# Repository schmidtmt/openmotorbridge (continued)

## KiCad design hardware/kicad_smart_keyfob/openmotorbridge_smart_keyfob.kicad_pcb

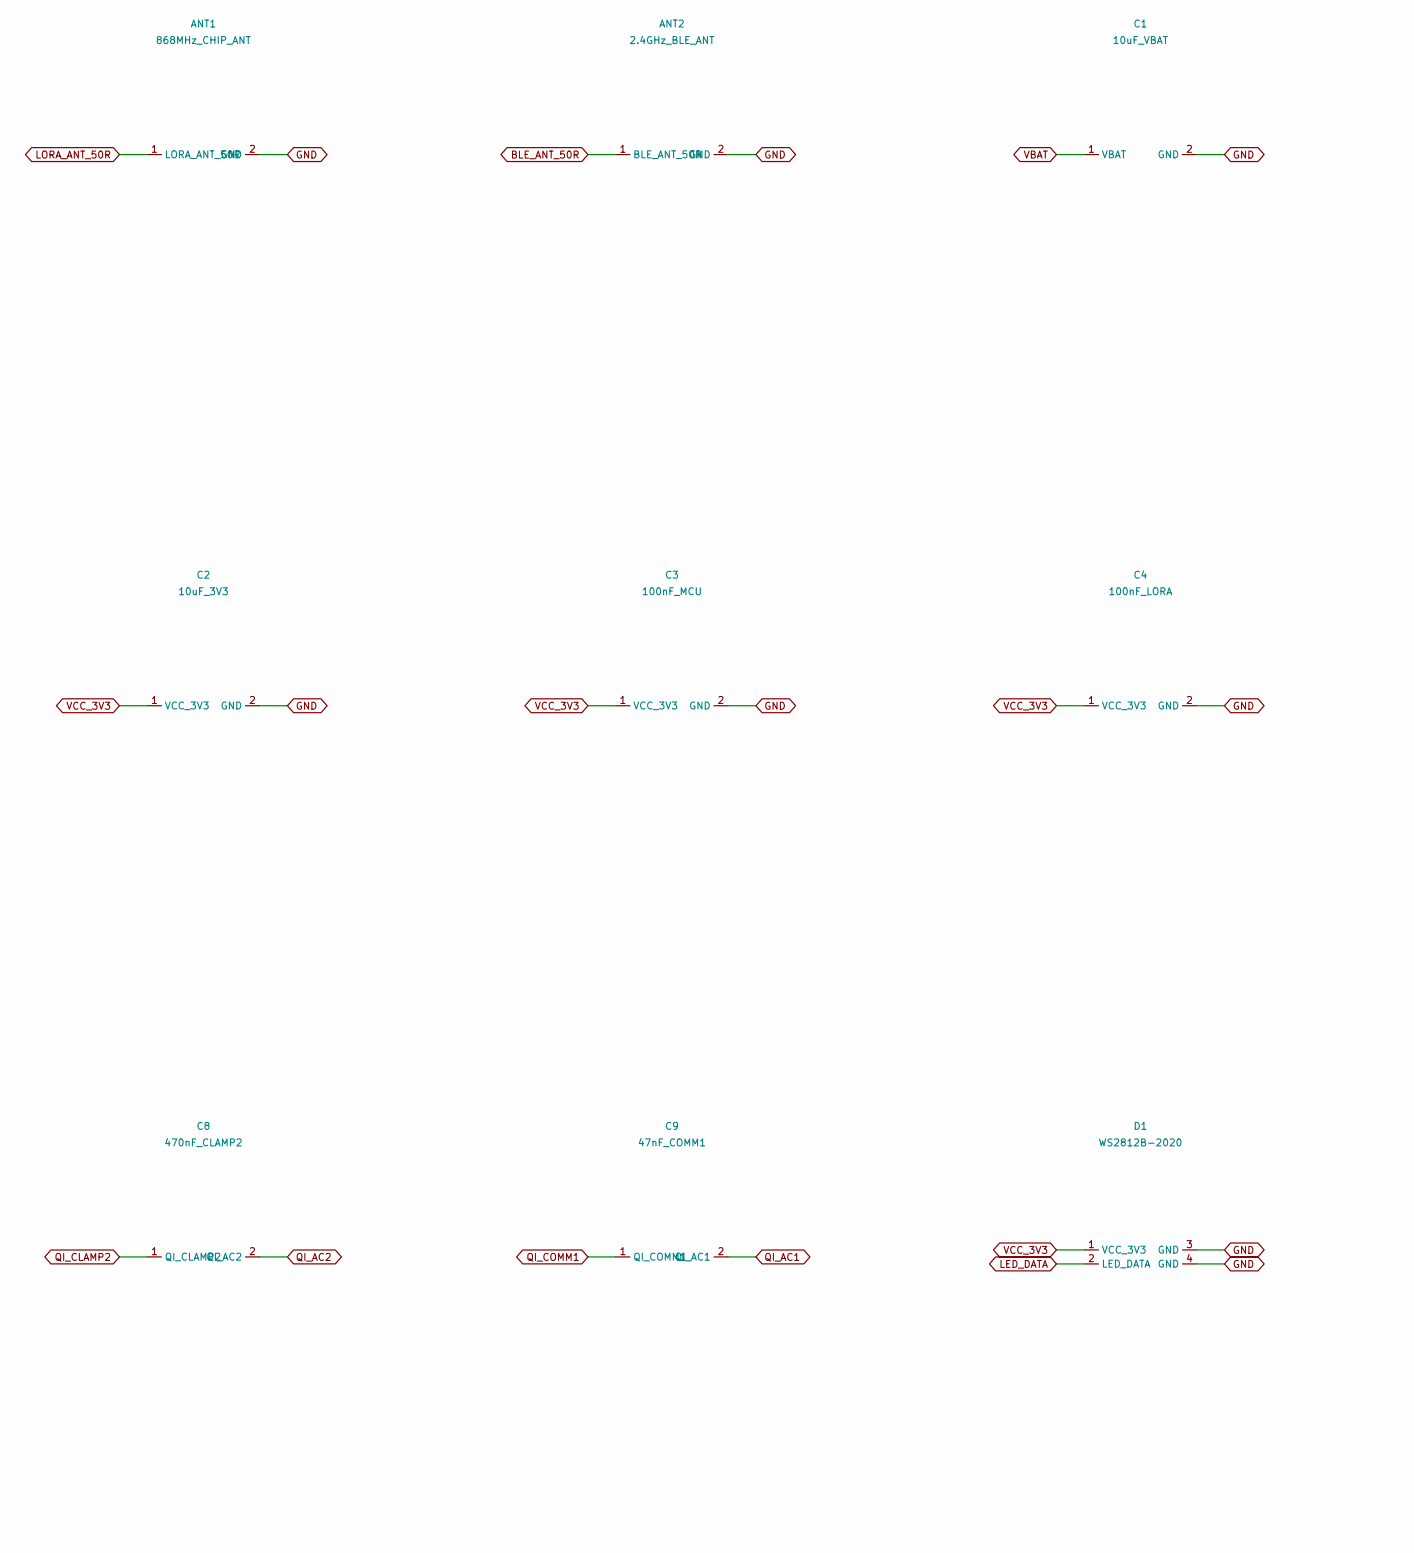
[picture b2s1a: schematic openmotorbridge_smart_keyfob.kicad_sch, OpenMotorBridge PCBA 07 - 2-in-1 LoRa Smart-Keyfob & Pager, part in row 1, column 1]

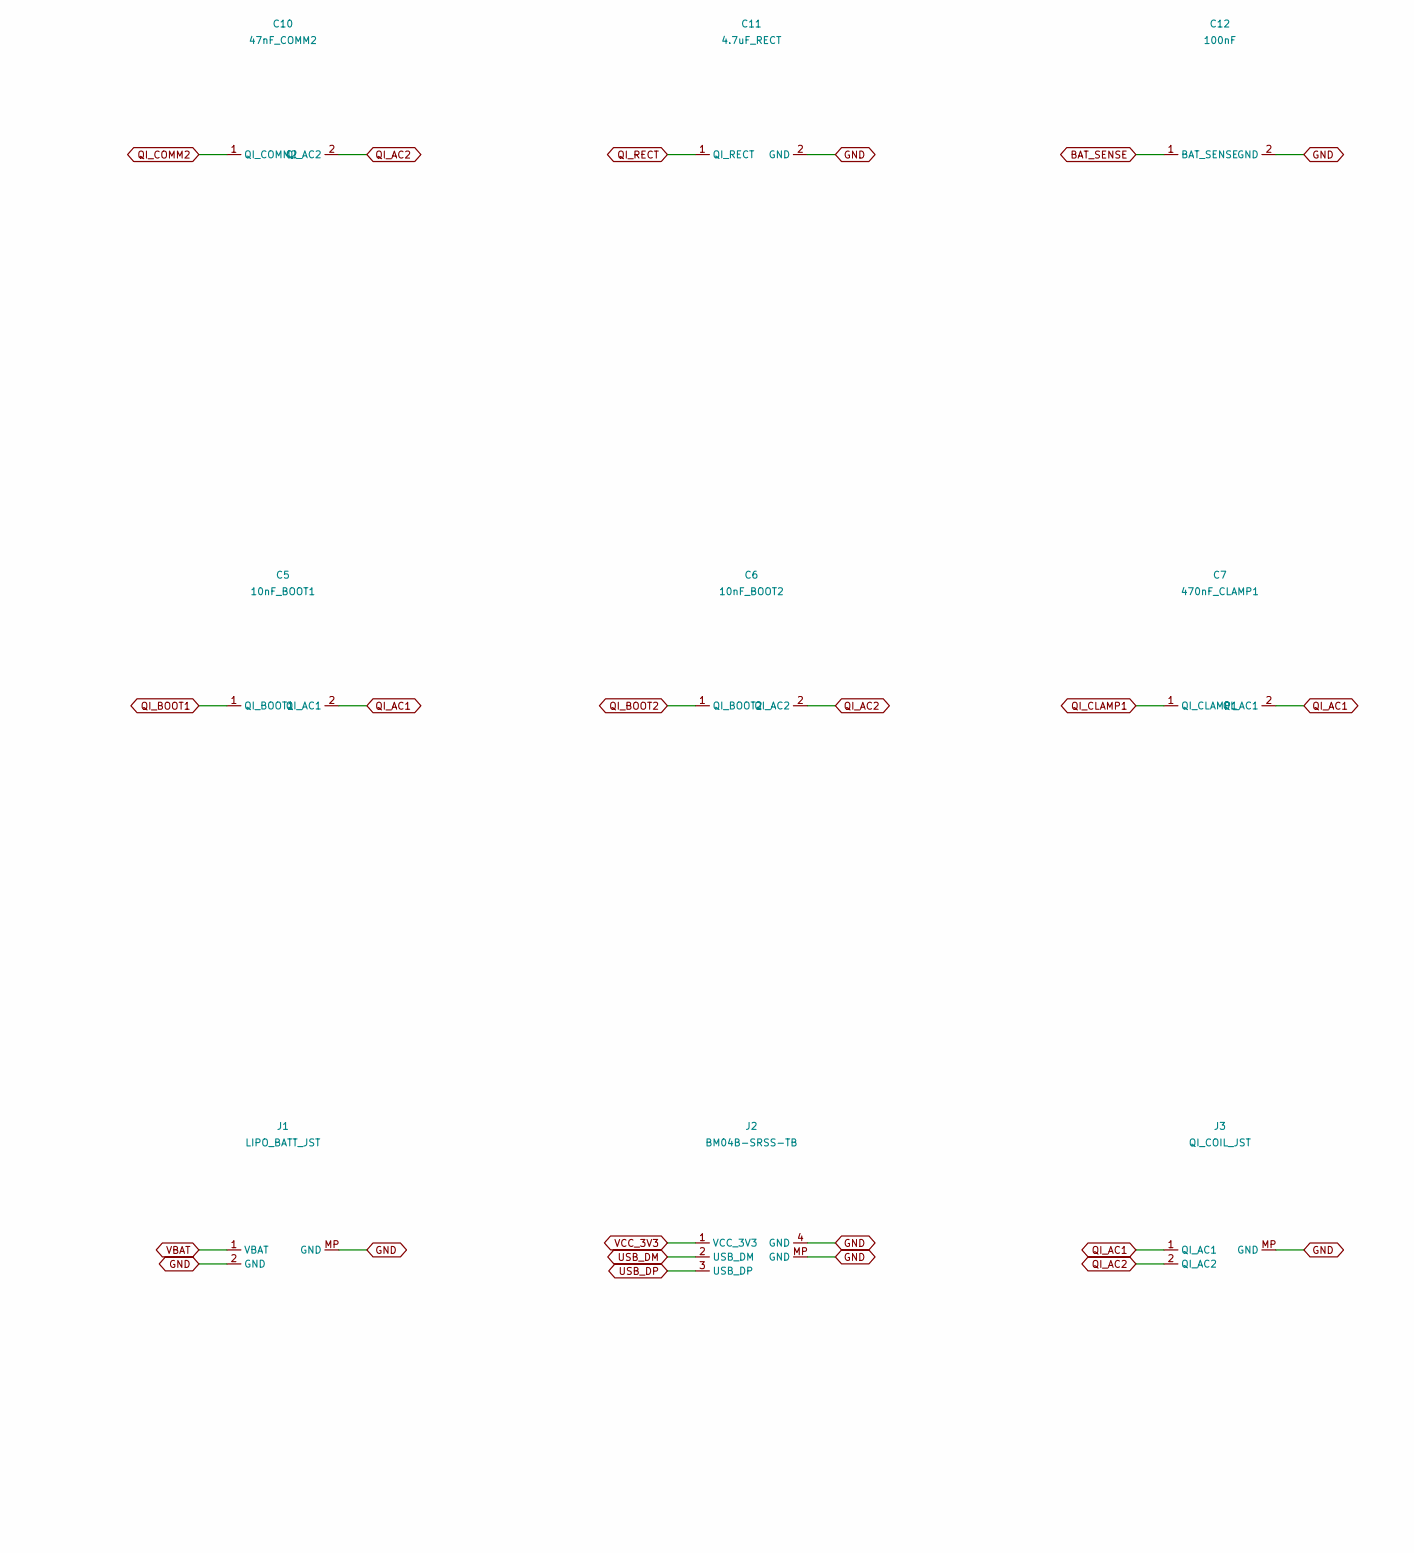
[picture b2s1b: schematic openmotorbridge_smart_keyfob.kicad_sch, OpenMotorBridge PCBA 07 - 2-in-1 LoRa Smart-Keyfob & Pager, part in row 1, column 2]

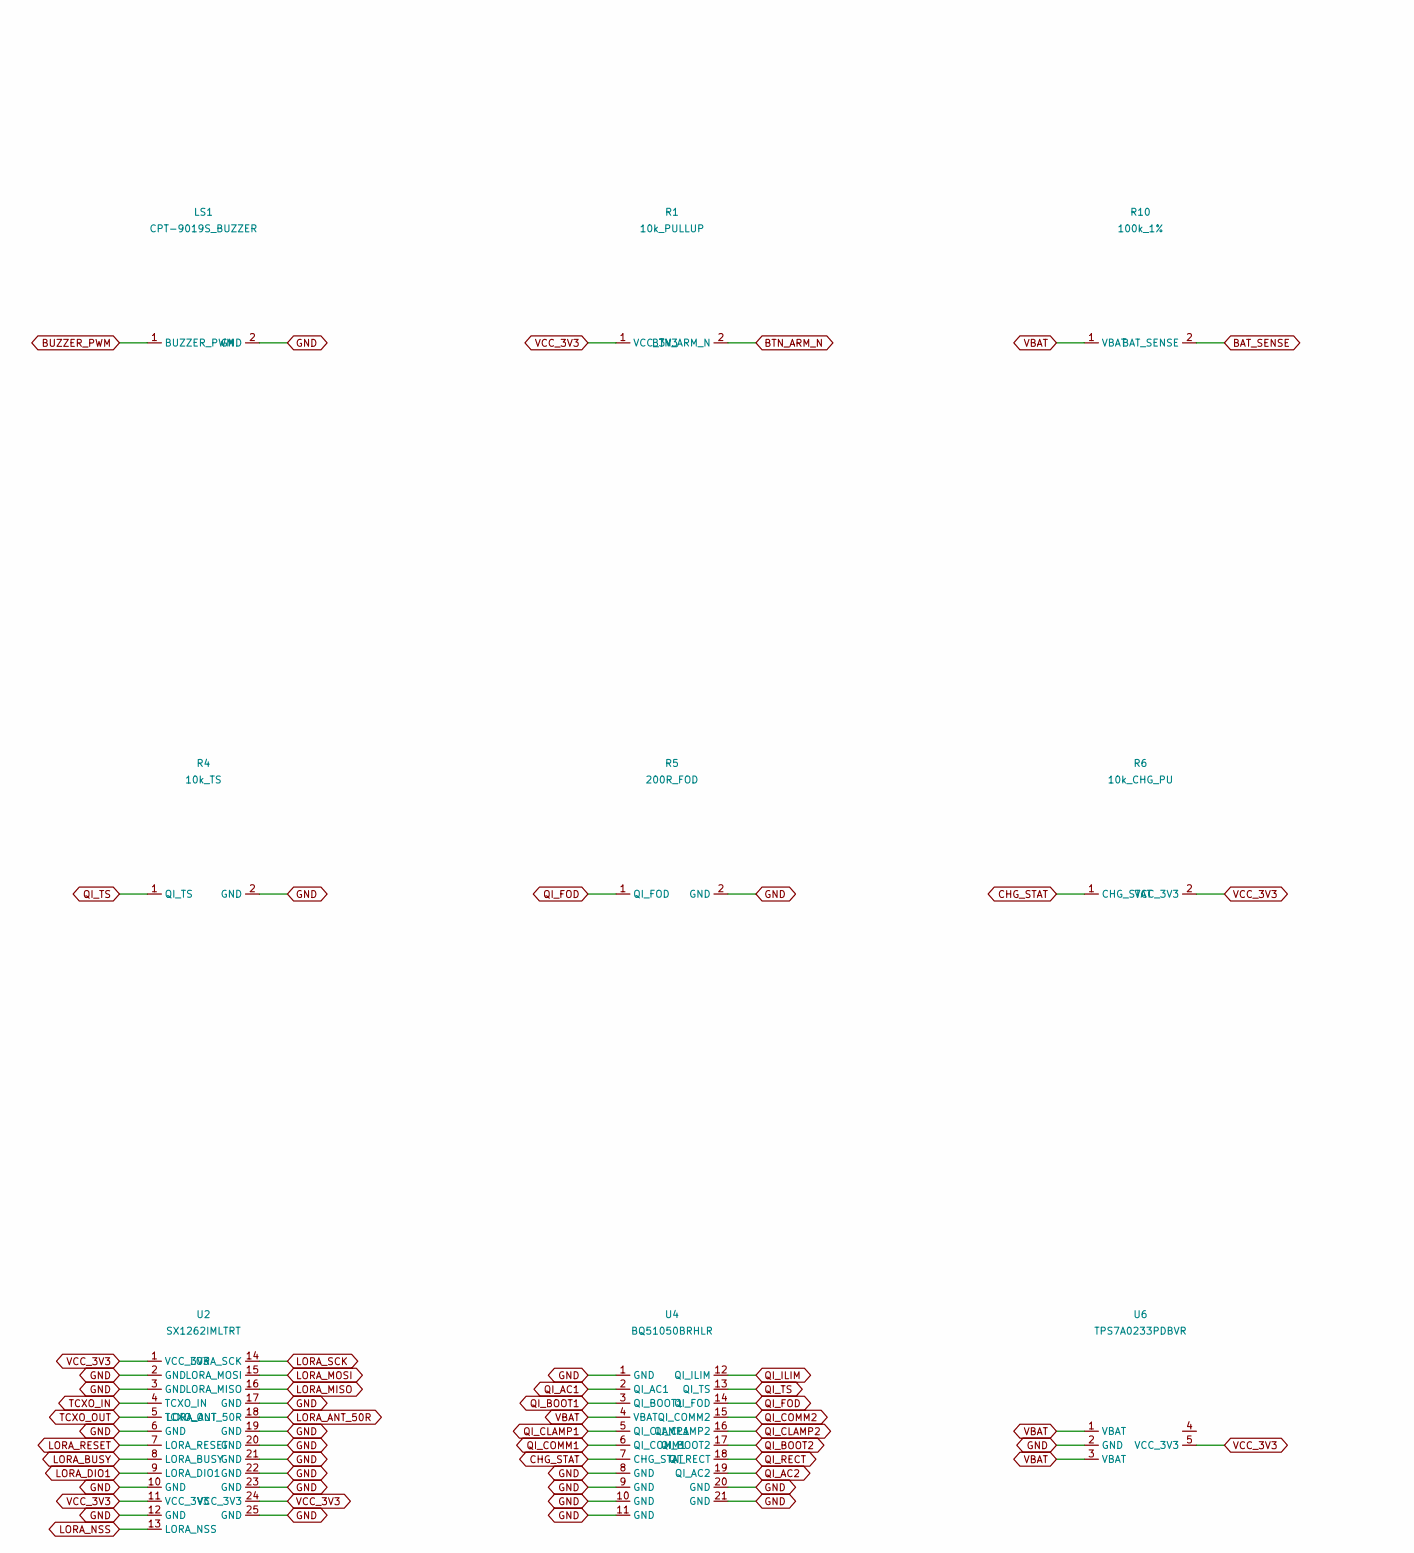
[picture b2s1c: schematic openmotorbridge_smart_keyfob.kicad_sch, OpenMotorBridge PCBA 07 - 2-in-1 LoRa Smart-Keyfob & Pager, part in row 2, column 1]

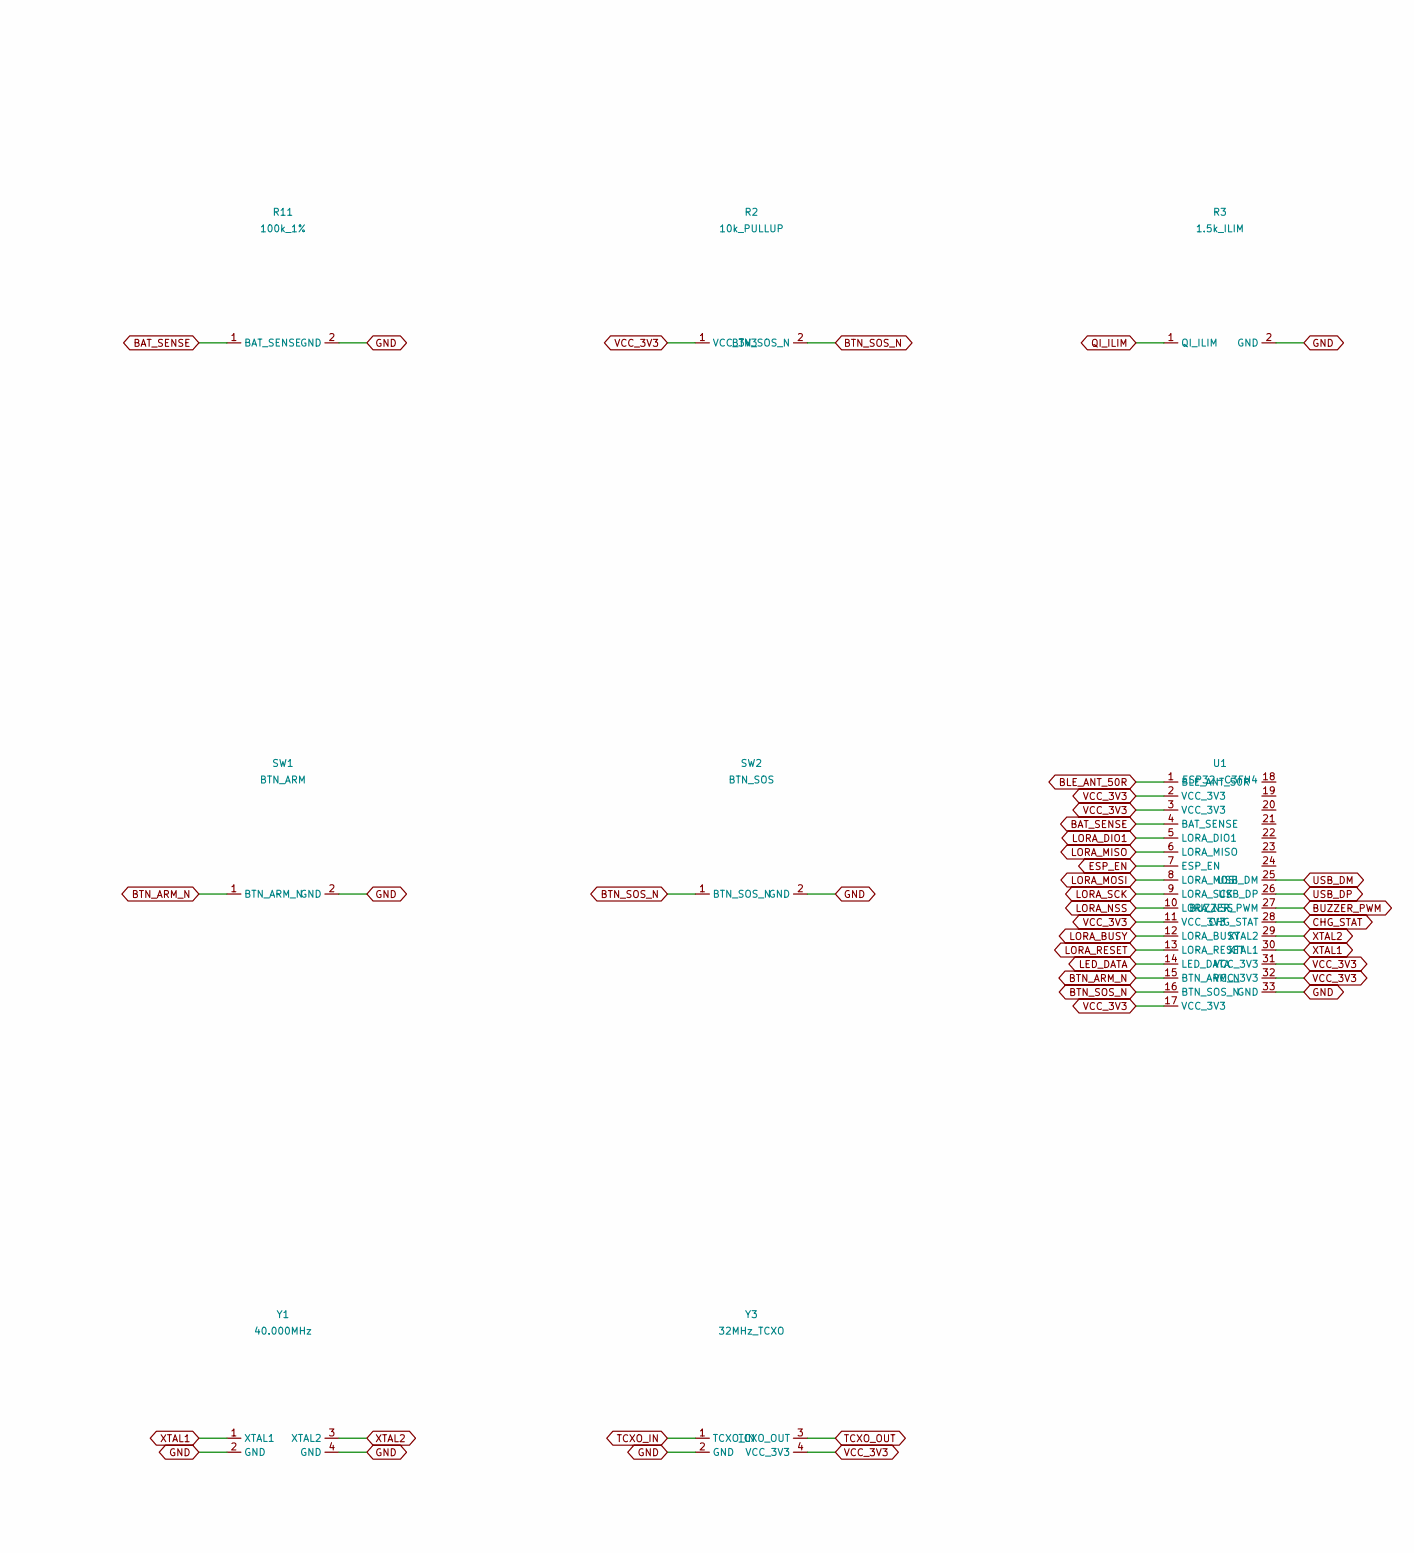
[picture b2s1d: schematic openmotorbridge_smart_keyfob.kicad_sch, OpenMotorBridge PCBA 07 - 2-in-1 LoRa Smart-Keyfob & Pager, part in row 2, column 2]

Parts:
ANT1: 868MHz_CHIP_ANT; R_0805_2012Metric
ANT2: 2.4GHz_BLE_ANT; R_0805_2012Metric
C1: 10uF_VBAT; C_0603_1608Metric
C2: 10uF_3V3; C_0603_1608Metric
C3: 100nF_MCU; C_0402_1005Metric
C4: 100nF_LORA; C_0402_1005Metric
C5: 10nF_BOOT1; C_0402_1005Metric
C6: 10nF_BOOT2; C_0402_1005Metric
C7: 470nF_CLAMP1; C_0402_1005Metric
C8: 470nF_CLAMP2; C_0402_1005Metric
C9: 47nF_COMM1; C_0402_1005Metric
C10: 47nF_COMM2; C_0402_1005Metric
C11: 4.7uF_RECT; C_0402_1005Metric
C12: 100nF; C_0402_1005Metric
D1: WS2812B-2020; LED_WS2812B-2020_PLCC4_2.0x2.0mm
J1: LIPO_BATT_JST; JST_SH_BM02B-SRSS-TB_1x02-1MP_P1.00mm_Vertical
J2: BM04B-SRSS-TB; JST_SH_BM04B-SRSS-TB_1x04-1MP_P1.00mm_Vertical
J3: QI_COIL_JST; JST_SH_BM02B-SRSS-TB_1x02-1MP_P1.00mm_Vertical
LS1: CPT-9019S_BUZZER; Buzzer_CUI_CPT-9019S-SMT
R1, R2: 10k_PULLUP; R_0402_1005Metric
R3: 1.5k_ILIM; R_0402_1005Metric
R4: 10k_TS; R_0402_1005Metric
R5: 200R_FOD; R_0402_1005Metric
R6: 10k_CHG_PU; R_0402_1005Metric
R10, R11: 100k_1%; R_0402_1005Metric
SW1: BTN_ARM; SW_Push_SPST_NO_Alps_SKRK
SW2: BTN_SOS; SW_Push_SPST_NO_Alps_SKRK
U1: ESP32-C3FH4; QFN-32-1EP_5x5mm_P0.5mm_EP3.7x3.7mm_ThermalVias
U2: SX1262IMLTRT; QFN-24-1EP_4x4mm_P0.5mm_EP2.8x2.8mm
U4: BQ51050BRHLR; Texas_VQFN-RHL-20_ThermalVias
U6: TPS7A0233PDBVR; SOT-23-5
Y1: 40.000MHz; Crystal_SMD_2016-4Pin_2.0x1.6mm
Y3: 32MHz_TCXO; Crystal_SMD_2016-4Pin_2.0x1.6mm

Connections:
BAT_SENSE: C12.1 (BAT_SENSE), R10.2 (BAT_SENSE), R11.1 (BAT_SENSE), U1.4 (BAT_SENSE)
BLE_ANT_50R: ANT2.1 (BLE_ANT_50R), U1.1 (BLE_ANT_50R)
BTN_ARM_N: R1.2 (BTN_ARM_N), SW1.1 (BTN_ARM_N), U1.15 (BTN_ARM_N)
BTN_SOS_N: R2.2 (BTN_SOS_N), SW2.1 (BTN_SOS_N), U1.16 (BTN_SOS_N)
BUZZER_PWM: LS1.1 (BUZZER_PWM), U1.27 (BUZZER_PWM)
CHG_STAT: R6.1 (CHG_STAT), U1.28 (CHG_STAT), U4.7 (CHG_STAT)
ESP_EN: U1.7 (ESP_EN)
GND: ANT1.2 (GND), ANT2.2 (GND), C1.2 (GND), C2.2 (GND), C3.2 (GND), C4.2 (GND), C11.2 (GND), C12.2 (GND), D1.3 (GND), D1.4 (GND), J1.2 (QI_AC2), J1.MP, J2.4 (GND), J2.MP, J3.MP, LS1.2 (GND), R3.2 (GND), R4.2 (GND), R5.2 (GND), R11.2 (GND), SW1.2 (GND), SW2.2 (GND), U1.33 (GND), U2.2 (GND), U2.3 (GND), U2.6 (GND), U2.10 (GND), U2.12 (GND), U2.17 (GND), U2.19 (GND), U2.20 (GND), U2.21 (GND), U2.22 (GND), U2.23 (GND), U2.25 (GND), U4.1 (GND), U4.8 (GND), U4.9 (GND), U4.10 (GND), U4.11 (GND), U4.20 (GND), U4.21 (GND), U6.2 (GND), Y1.2 (GND), Y1.4 (GND), Y3.2 (GND)
LED_DATA: D1.2 (LED_DATA), U1.14 (LED_DATA)
LORA_ANT_50R: ANT1.1 (LORA_ANT_50R), U2.18 (LORA_ANT_50R)
LORA_BUSY: U1.12 (LORA_BUSY), U2.8 (LORA_BUSY)
LORA_DIO1: U1.5 (LORA_DIO1), U2.9 (LORA_DIO1)
LORA_MISO: U1.6 (LORA_MISO), U2.16 (LORA_MISO)
LORA_MOSI: U1.8 (LORA_MOSI), U2.15 (LORA_MOSI)
LORA_NSS: U1.10 (LORA_NSS), U2.13 (LORA_NSS)
LORA_RESET: U1.13 (LORA_RESET), U2.7 (LORA_RESET)
LORA_SCK: U1.9 (LORA_SCK), U2.14 (LORA_SCK)
QI_AC1: C5.2 (QI_AC1), C7.2 (QI_AC1), C9.2 (QI_AC1), J3.1 (VBAT), U4.2 (QI_AC1)
QI_AC2: C6.2 (QI_AC2), C8.2 (QI_AC2), C10.2 (QI_AC2), J3.2 (GND), U4.19 (QI_AC2)
QI_BOOT1: C5.1 (QI_BOOT1), U4.3 (QI_BOOT1)
QI_BOOT2: C6.1 (QI_BOOT2), U4.17 (QI_BOOT2)
QI_CLAMP1: C7.1 (QI_CLAMP1), U4.5 (QI_CLAMP1)
QI_CLAMP2: C8.1 (QI_CLAMP2), U4.16 (QI_CLAMP2)
QI_COMM1: C9.1 (QI_COMM1), U4.6 (QI_COMM1)
QI_COMM2: C10.1 (QI_COMM2), U4.15 (QI_COMM2)
QI_FOD: R5.1 (QI_FOD), U4.14 (QI_FOD)
QI_ILIM: R3.1 (QI_ILIM), U4.12 (QI_ILIM)
QI_RECT: C11.1 (QI_RECT), U4.18 (QI_RECT)
QI_TS: R4.1 (QI_TS), U4.13 (QI_TS)
TCXO_IN: U2.4 (TCXO_IN), Y3.1 (TCXO_IN)
TCXO_OUT: U2.5 (TCXO_OUT), Y3.3 (TCXO_OUT)
USB_DM: J2.2 (USB_DM), U1.25 (USB_DM)
USB_DP: J2.3 (USB_DP), U1.26 (USB_DP)
VBAT: C1.1 (VBAT), J1.1 (QI_AC1), R10.1 (VBAT), U4.4 (VBAT), U6.1 (VBAT), U6.3 (EN)
VCC_3V3: C2.1 (VCC_3V3), C3.1 (VCC_3V3), C4.1 (VCC_3V3), D1.1 (VCC_3V3), J2.1 (VCC_3V3), R1.1 (VCC_3V3), R2.1 (VCC_3V3), R6.2 (VCC_3V3), U1.2 (VCC_3V3), U1.3 (VCC_3V3), U1.11 (VCC_3V3), U1.17 (VCC_3V3), U1.31 (VCC_3V3), U1.32 (VCC_3V3), U2.1 (VCC_3V3), U2.11 (VCC_3V3), U2.24 (VCC_3V3), U6.5 (VCC_3V3), Y3.4 (VCC_3V3)
XTAL1: U1.30 (XTAL1), Y1.1 (XTAL1)
XTAL2: U1.29 (XTAL2), Y1.3 (XTAL2)

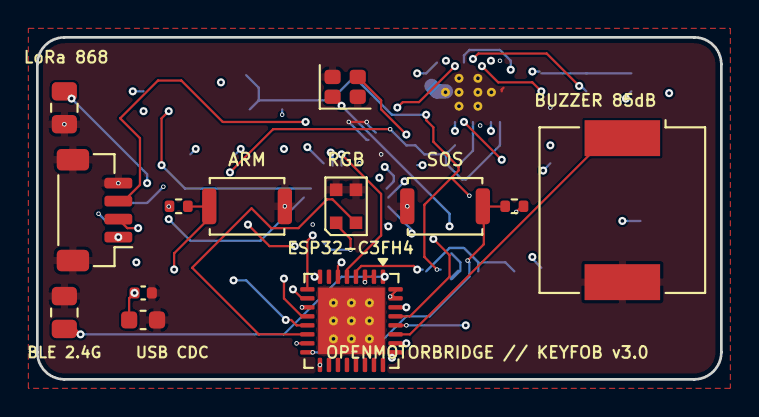
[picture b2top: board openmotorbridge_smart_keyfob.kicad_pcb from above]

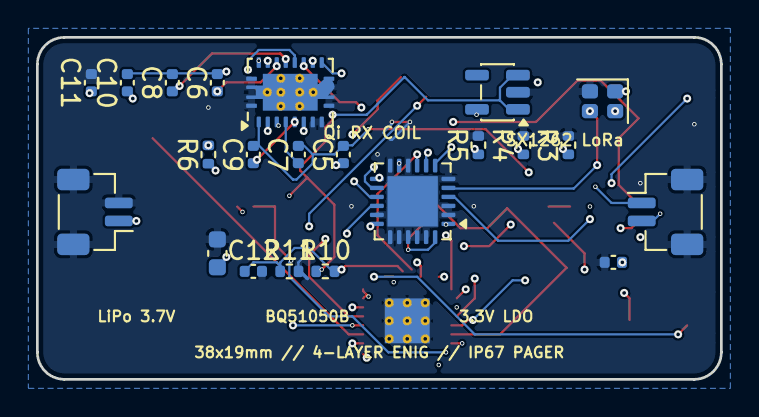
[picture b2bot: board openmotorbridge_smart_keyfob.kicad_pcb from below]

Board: 4 copper layers, 38.0 x 19.0 mm, 35 parts (22 on the bottom side), 36 nets.

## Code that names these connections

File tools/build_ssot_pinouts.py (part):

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                "pin_description_url": OFFICIAL_CHIPS["USB2517I"]["pin_description_url"],
                "table_ref": OFFICIAL_CHIPS["USB2517I"]["table_ref"],
                "pins": [
                    {"pad": "2", "pin_name": "RESET_N", "net": "HUB_RESET_N", "type": "Control In", "target": "U2 (ESP32-S31)", "spec": "Active-Low Hardware Reset via GPIO"},
                    {"pad": "8", "pin_name": "USBDN_DM7", "net": "USBC_DM", "type": "USB D-", "target": "J3 (USB-C Service)", "spec": "Port 7 Downstream USB D-"},
                    {"pad": "9", "pin_name": "USBDN_DP7", "net": "USBC_DP", "type": "USB D+", "target": "J3 (USB-C Service)", "spec": "Port 7 Downstream USB D+" },
                    {"pad": "16", "pin_name": "USBUP_DM", "net": "ESP_USB_DM", "type": "USB D-", "target": "U2.54 (ESP32-S31)", "spec": "Upstream Port USB High-Speed D-"},
                    {"pad": "17", "pin_name": "USBUP_DP", "net": "ESP_USB_DP", "type": "USB D+", "target": "U2.55 (ESP32-S31)", "spec": "Upstream Port USB High-Speed D+"},
                    {"pad": "24", "pin_name": "USBDN_DM1", "net": "BUS1_DM", "type": "USB D-", "target": "J6.3 (Strang 1 Front)", "spec": "Port 1 Downstream USB D-"},
                    {"pad": "25", "pin_name": "USBDN_DP1", "net": "BUS1_DP", "type": "USB D+", "target": "J6.4 (Strang 1 Front)", "spec": "Port 1 Downstream USB D+"},
                    {"pad": "32", "pin_name": "USBDN_DM2", "net": "BUS2_DM", "type": "USB D-", "target": "J6.7 (Strang 2 Pod L)", "spec": "Port 2 Downstream USB D-"},
                    {"pad": "33", "pin_name": "USBDN_DP2", "net": "BUS2_DP", "type": "USB D+", "target": "J6.8 (Strang 2 Pod L)", "spec": "Port 2 Downstream USB D+"},
                    {"pad": "40", "pin_name": "USBDN_DM3", "net": "BUS3_DM", "type": "USB D-", "target": "J6.11 (Strang 3 Pod R)", "spec": "Port 3 Downstream USB D-"},
                    {"pad": "41", "pin_name": "USBDN_DP3", "net": "BUS3_DP", "type": "USB D+", "target": "J6.12 (Strang 3 Pod R)", "spec": "Port 3 Downstream USB D+"},
                    {"pad": "48", "pin_name": "USBDN_DM4", "net": "BUS4_DM", "type": "USB D-", "target": "J6.15 (Strang 4 Radar)", "spec": "Port 4 Downstream USB D-"},
                    {"pad": "49", "pin_name": "USBDN_DP4", "net": "BUS4_DP", "type": "USB D+", "target": "J6.16 (Strang 4 Radar)", "spec": "Port 4 Downstream USB D+"},
                    {"pad": "56", "pin_name": "USBDN_DM5", "net": "BT_USB_DM", "type": "USB D-", "target": "U9.13 (QCC3086)", "spec": "Port 5 Downstream USB D- an Qualcomm BT Audio SoC"},
                    {"pad": "57", "pin_name": "USBDN_DP5", "net": "BT_USB_DP", "type": "USB D+", "target": "U9.14 (QCC3086)", "spec": "Port 5 Downstream USB D+ an Qualcomm BT Audio SoC"},
                    {"pad": "60", "pin_name": "USBDN_DM6", "net": "RES_USB_DM", "type": "USB D-", "target": "J7.3 (Reserve)", "spec": "Port 6 Downstream USB D-"},
                    {"pad": "61", "pin_name": "USBDN_DP6", "net": "RES_USB_DP", "type": "USB D+", "target": "J7.4 (Reserve)", "spec": "Port 6 Downstream USB D+"}
                ]
            },
            "U9": {
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                "pin_description_url": OFFICIAL_CHIPS["QCC3086"]["pin_description_url"],
                "table_ref": OFFICIAL_CHIPS["QCC3086"]["table_ref"],
                "pins": [
                    {"pad": "3", "pin_name": "I2S_MCLK", "net": "I2S_MCLK", "type": "Clock In", "target": "U2 (ESP32-S31)", "spec": "I2S Master Clock 12.288 MHz"},
                    {"pad": "4", "pin_name": "I2S_BCLK", "net": "I2S_BCLK", "type": "Clock In", "target": "U2 (ESP32-S31)", "spec": "I2S Bit Clock 3.072 MHz"},
                    {"pad": "5", "pin_name": "I2S_WS", "net": "I2S_WS", "type": "Sync In", "target": "U2 (ESP32-S31)", "spec": "I2S Word Select / LRCLK 48 kHz"},
                    {"pad": "6", "pin_name": "I2S_DOUT", "net": "I2S_DOUT", "type": "Audio In", "target": "U2 (ESP32-S31)", "spec": "Digital Audio Stream vom Smartphone (A2DP / Anrufer) an ESP32-S31 DSP"},
                    {"pad": "7", "pin_name": "I2S_DIN", "net": "I2S_DIN", "type": "Audio Out", "target": "U2 (ESP32-S31)", "spec": "Helmmikrofon-Audio Stream an QCC3086 Voice-Backchannel zum Smartphone"},
                    {"pad": "9", "pin_name": "UART_TX", "net": "BT_UART_TX", "type": "UART Out", "target": "U2 (ESP32-S31)", "spec": "HCI / AT-Befehle TX zum ESP32-S31"},
                    {"pad": "10", "pin_name": "UART_RX", "net": "BT_UART_RX", "type": "UART In", "target": "U2 (ESP32-S31)", "spec": "HCI / AT-Befehle RX vom ESP32-S31"},
                    {"pad": "11", "pin_name": "CHIP_EN", "net": "BT_EN", "type": "Control In", "target": "U2 (ESP32-S31)", "spec": "Power Enable Active High"},
                    {"pad": "13", "pin_name": "USB_DM", "net": "BT_USB_DM", "type": "USB D-", "target": "U8.56 (Hub Port 5)", "spec": "USB Audio Class 2.0 / DFU Datenleitung D-"},
                    {"pad": "14", "pin_name": "USB_DP", "net": "BT_USB_DP", "type": "USB D+", "target": "U8.57 (Hub Port 5)", "spec": "USB Audio Class 2.0 / DFU Datenleitung D+"},
                    {"pad": "15", "pin_name": "RF_ANT", "net": "BT_RF_AUDIO", "type": "RF 2.4 GHz", "target": "ANT2 (U.FL)", "spec": "Bluetooth 5.4 Antennenport an ANT2 Deckelantenne (Smartphone-Link)"}
                ]
            },
            "U13": {
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                "pin_description_url": OFFICIAL_CHIPS["QCC3086"]["pin_description_url"],
                "table_ref": OFFICIAL_CHIPS["QCC3086"]["table_ref"],
                "pins": [
                    {"pad": "4", "pin_name": "I2S_BCLK", "net": "I2S_BCLK", "type": "Clock In", "target": "U2 (ESP32-S31)", "spec": "I2S Bit Clock 3.072 MHz"},
                    {"pad": "5", "pin_name": "I2S_WS", "net": "I2S_WS", "type": "Sync In", "target": "U2 (ESP32-S31)", "spec": "I2S Word Select / LRCLK 48 kHz"},
                    {"pad": "6", "pin_name": "I2S_DOUT", "net": "HELM1_I2S_DOUT", "type": "Audio In", "target": "U2 (ESP32-S31)", "spec": "Audio-Stream vom DSP an Helm 1"},
                    {"pad": "7", "pin_name": "I2S_DIN", "net": "HELM1_I2S_DIN", "type": "Audio Out", "target": "U2 (ESP32-S31)", "spec": "Helm 1 Mikrofon-Rückkanal an DSP"},
                    {"pad": "9", "pin_name": "UART_TX", "net": "HELM1_BT_UART_TX", "type": "UART Out", "target": "U2 (ESP32-S31)", "spec": "HCI / AT TX Helm 1"},
                    {"pad": "10", "pin_name": "UART_RX", "net": "HELM1_BT_UART_RX", "type": "UART In", "target": "U2 (ESP32-S31)", "spec": "HCI / AT RX Helm 1"},
                    {"pad": "11", "pin_name": "CHIP_EN", "net": "HELM1_BT_EN", "type": "Control In", "target": "U2 (ESP32-S31)", "spec": "Power Enable Helm 1"},
                    {"pad": "13", "pin_name": "USB_DM", "net": "HELM1_USB_DM", "type": "USB D-", "target": "U8 (Hub)", "spec": "USB D- Helm 1"},
                    {"pad": "14", "pin_name": "USB_DP", "net": "HELM1_USB_DP", "type": "USB D+", "target": "U8 (Hub)", "spec": "USB D+ Helm 1"},
                    {"pad": "15", "pin_name": "RF_ANT", "net": "BT_RF_HELM1", "type": "RF 2.4 GHz", "target": "ANT3 (Keramik)", "spec": "BT 5.4 RF Port an Keramikantenne ANT3"}
                ]
            },
            "U14": {
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                "pin_description_url": OFFICIAL_CHIPS["QCC3086"]["pin_description_url"],
                "table_ref": OFFICIAL_CHIPS["QCC3086"]["table_ref"],
                "pins": [
                    {"pad": "4", "pin_name": "I2S_BCLK", "net": "I2S_BCLK", "type": "Clock In", "target": "U2 (ESP32-S31)", "spec": "I2S Bit Clock 3.072 MHz"},
                    {"pad": "5", "pin_name": "I2S_WS", "net": "I2S_WS", "type": "Sync In", "target": "U2 (ESP32-S31)", "spec": "I2S Word Select / LRCLK 48 kHz"},
                    {"pad": "6", "pin_name": "I2S_DOUT", "net": "HELM2_I2S_DOUT", "type": "Audio In", "target": "U2 (ESP32-S31)", "spec": "Audio-Stream vom DSP an Helm 2"},
                    {"pad": "7", "pin_name": "I2S_DIN", "net": "HELM2_I2S_DIN", "type": "Audio Out", "target": "U2 (ESP32-S31)", "spec": "Helm 2 Mikrofon-Rückkanal an DSP"},
                    {"pad": "9", "pin_name": "UART_TX", "net": "HELM2_BT_UART_TX", "type": "UART Out", "target": "U2 (ESP32-S31)", "spec": "HCI / AT TX Helm 2"},
                    {"pad": "10", "pin_name": "UART_RX", "net": "HELM2_BT_UART_RX", "type": "UART In", "target": "U2 (ESP32-S31)", "spec": "HCI / AT RX Helm 2"},
                    {"pad": "11", "pin_name": "CHIP_EN", "net": "HELM2_BT_EN", "type": "Control In", "target": "U2 (ESP32-S31)", "spec": "Power Enable Helm 2"},
                    {"pad": "13", "pin_name": "USB_DM", "net": "HELM2_USB_DM", "type": "USB D-", "target": "U8 (Hub)", "spec": "USB D- Helm 2"},
                    {"pad": "14", "pin_name": "USB_DP", "net": "HELM2_USB_DP", "type": "USB D+", "target": "U8 (Hub)", "spec": "USB D+ Helm 2"},
                    {"pad": "15", "pin_name": "RF_ANT", "net": "BT_RF_HELM2", "type": "RF 2.4 GHz", "target": "ANT4 (Keramik)", "spec": "BT 5.4 RF Port an Keramikantenne ANT4"}
                ]
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
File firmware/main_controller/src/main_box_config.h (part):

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// 1. Native USB 2.0 High-Speed / Full-Speed Interface -> U8 (USB2517I-JZX Port 1)
// Upstream of U8 is J3 (Single External USB-C Service & DFU Port for Entire Bike)
// -----------------------------------------------------------------------------
#define PIN_MAIN_USB_DM                 GPIO_NUM_19  // U2 Pad 13 -> U8 Pin 16 (ESP_USB_DM)
#define PIN_MAIN_USB_DP                 GPIO_NUM_20  // U2 Pad 14 -> U8 Pin 17 (ESP_USB_DP)

// -----------------------------------------------------------------------------
// 2. Ignition Sense (KL15), Pairing Button (SW1) & Status RGB LED (D1 / J4)
// -----------------------------------------------------------------------------
#define PIN_MAIN_KL15_SENSE             GPIO_NUM_3   // U2 Pad 5 (GPIO3) -> R3/D4/Q1 Ignition Sense (KL15_SENSE)
#define PIN_MAIN_BOOT_PAIR_BTN          GPIO_NUM_0   // U2 Pad 27 -> SW1 Pairing / Boot Button (ESP_BOOT)
#define PIN_MAIN_RGB_LED_DATA           GPIO_NUM_48  // U2 Pad 28 -> D1 & J4 WS2812B-2020 (RGB_LED_DATA)

// -----------------------------------------------------------------------------
// 3. UPS LiPo Charger (U4 BQ24075RGTR), 10k NTC Guard (J5) & Dual-Power (D3 LM66100)
// -----------------------------------------------------------------------------
#define PIN_MAIN_BAT_SENSE_ADC          GPIO_NUM_1   // U2 Pad 31 -> R12/R13 Voltage Divider (BAT_SENSE)
#define PIN_MAIN_BAT_NTC_ADC            GPIO_NUM_15  // U2 Pad 25 -> J5 Pin 3 10k NTC Thermistor (BAT_NTC)
// JEITA LiPo Temperature Limits: Charge allowed only between 0.0 °C and +45.0 °C
#define MAIN_LIPO_JEITA_MIN_TEMP_C      0.0f
#define MAIN_LIPO_JEITA_MAX_TEMP_C      45.0f
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// 4. Shared Internal I2C Bus (U3 ES8388 Codec, U5 Bosch BMI270 IMU)
// -----------------------------------------------------------------------------
#define MAIN_I2C_PORT                   I2C_NUM_0
#define PIN_MAIN_I2C_SDA                GPIO_NUM_22  // U2 Pad 17 (GPIO22) -> U3 Pin 28, U5 Pin 13 (I2C_SDA)
#define PIN_MAIN_I2C_SCL                GPIO_NUM_23  // U2 Pad 18 (GPIO23) -> U3 Pin 27, U5 Pin 12 (I2C_SCL)
#define I2C_ADDR_ES8388_CODEC           0x10         // U3 Everest ES8388 24-Bit Audio Codec
#define I2C_ADDR_BMI270_IMU             0x68         // U5 Bosch BMI270 6-Axis IMU + Hardware Step/Shock Interrupt

// -----------------------------------------------------------------------------
// 5. Master TDM / I2S Audio Bus (Shared by U3 ES8388 & Triple Qualcomm QCC3086)
// -----------------------------------------------------------------------------
#define PIN_MAIN_I2S_MCLK               GPIO_NUM_35  // U2 Pad 12 (GPIO35) -> U3 Pin 1 / QCC3086 Pin 1 (I2S_MCLK)
#define PIN_MAIN_I2S_BCLK               GPIO_NUM_16  // U2 Pad 30 -> U3 Pin 2 / QCC3086 Pin 2 (I2S_BCLK)
#define PIN_MAIN_I2S_WS                 GPIO_NUM_47  // U2 Pad 32 -> U3 Pin 3 / QCC3086 Pin 3 (I2S_WS)
#define PIN_MAIN_I2S_DOUT               GPIO_NUM_17  // U2 Pad 15 -> U3 Pin 4 / QCC3086 Pin 4 (I2S_DOUT)
#define PIN_MAIN_I2S_DIN                GPIO_NUM_18  // U2 Pad 16 -> U3 Pin 5 / QCC3086 Pin 5 (I2S_DIN)

// -----------------------------------------------------------------------------
// 6. Qualcomm QCC3086 Bluetooth 5.4 Triple-SoC Hub (PCBA 01)
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// -----------------------------------------------------------------------------
#define QCC3086_UART_PORT               UART_NUM_1
#define QCC3084_UART_PORT               QCC3086_UART_PORT
#define PIN_MAIN_BT_EN                  GPIO_NUM_1   // U2 Pad 9  -> QCC3086 Pin 11 (BT_EN)
#define PIN_MAIN_BT_UART_RX             GPIO_NUM_2   // U2 Pad 10 -> QCC3086 Pin 10 (BT_UART_RX)
#define PIN_MAIN_BT_UART_TX             GPIO_NUM_3   // U2 Pad 11 -> QCC3086 Pin 9  (BT_UART_TX)

// -----------------------------------------------------------------------------
// 7. Onboard Semtech SX1262IMLTRT 868 MHz LoRa Transceiver (U10, +22 dBm)
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// at KiCad (X=176.03, Y=74.75) routed to external lid 868MHz dipole.
// -----------------------------------------------------------------------------
#define MAIN_LORA_SPI_HOST              SPI2_HOST
#define PIN_MAIN_LORA_SCK               GPIO_NUM_2   // U2 Pad 4 (GPIO2) -> U10 Pin 20 (SPI_SCK)
#define PIN_MAIN_LORA_MISO              GPIO_NUM_4   // U2 Pad 6 (GPIO4) -> U10 Pin 18 (SPI_MISO)
#define PIN_MAIN_LORA_MOSI              GPIO_NUM_5   // U2 Pad 7 (GPIO5) -> U10 Pin 19 (SPI_MOSI)
#define PIN_MAIN_LORA_NSS               GPIO_NUM_10  // U2 Pad 24 -> U10 Pin 21 (LORA_NSS)
#define PIN_MAIN_LORA_RST               GPIO_NUM_7   // U2 Pad 23 -> U10 Pin 1  (LORA_RST)
#define PIN_MAIN_LORA_BUSY              GPIO_NUM_21  // U2 Pad 20 -> U10 Pin 14 (LORA_BUSY)
#define PIN_MAIN_LORA_DIO1              GPIO_NUM_14  // U2 Pad 19 -> U10 Pin 15 (LORA_DIO1)

// -----------------------------------------------------------------------------
// 7b. On-Board 2.4 GHz BLE Control Antenna (ANT3 Johanson 2450AT18D0100)
// Dedicated SMD ceramic chip antenna (3.2 x 1.6 mm) on left board edge
// at KiCad (X=117.80, Y=88.25, rot=180 deg) with feed pad facing inward.
// Driven directly from U2 ESP32-S31-WROOM-1U Pin 63 (BLE_RF_2G4).
// Handles vehicle control: Pods, Action Cam, TPMS & Smart Keyfob proximity.
// Separated by >65 mm from ANT1 (LoRa) and ANT2 (Helmaudio) to prevent desense.
// -----------------------------------------------------------------------------
#define MAIN_BLE_ANTENNA_TYPE           "Johanson_2450AT18D0100_Ceramic_SMD"
#define MAIN_BLE_RF_PIN_U2_PAD          63           // ESP32-S31 Pad 63 (BLE_RF_2G4)

// -----------------------------------------------------------------------------
// 8. Automotive CAN-FD Transceiver (U6 TI TCAN334GDCNT -> J1 Pin 3/4)
// -----------------------------------------------------------------------------
#define PIN_MAIN_CAN_TX                 GPIO_NUM_26  // U2 Pad 21 (GPIO 26) -> U6 Pin 1 (CAN_TX)
#define PIN_MAIN_CAN_RX                 GPIO_NUM_27  // U2 Pad 22 (GPIO 27) -> U6 Pin 4 (CAN_RX)

// -----------------------------------------------------------------------------
// 9. High-Speed 4-Bit SDIO MicroSD Blackbox Slot (J2 Hirose DM3D-SF)
// -----------------------------------------------------------------------------
#define PIN_MAIN_SD_DAT1                GPIO_NUM_33  // U2 Pad 33 -> J2 Pin 8 (SD_DAT1)
#define PIN_MAIN_SD_DAT2                GPIO_NUM_34  // U2 Pad 34 -> J2 Pin 1 (SD_DAT2)
#define PIN_MAIN_SD_CLK                 GPIO_NUM_55  // U2 Pad 35 (GPIO55) -> J2 Pin 5 (SD_CLK)
#define PIN_MAIN_SD_CMD                 GPIO_NUM_36  // U2 Pad 36 -> J2 Pin 3 (SD_CMD)
#define PIN_MAIN_SD_DAT0                GPIO_NUM_37  // U2 Pad 37 -> J2 Pin 7 (SD_DAT0)
#define PIN_MAIN_SD_DAT3                GPIO_NUM_38  // U2 Pad 38 -> J2 Pin 2 (SD_DAT3)
#define PIN_MAIN_SD_CD                  GPIO_NUM_39  // U2 Pad 39 -> J2 Pin 9 (SD_CD Card Detect)

// -----------------------------------------------------------------------------
// 10. Triple-QCC3086 Bluetooth Audio Engine (U9 Phone Link, U13 Helm 1, U14 Helm 2)
// Independent QCC3086 transceivers for phone audio and dual helmet intercom/music links.
// -----------------------------------------------------------------------------
#define QCC_HELM1_UART_PORT             UART_NUM_2
#define PIN_MAIN_HELM1_UART_TX          GPIO_NUM_33  // U2 Pad 13 (GPIO33) -> U13 Pin 41 (HELM1_UART_TX)
#define PIN_MAIN_HELM1_UART_RX          GPIO_NUM_34  // U2 Pad 14 (GPIO34) -> U13 Pin 40 (HELM1_UART_RX)
#define PIN_MAIN_HELM1_EN               GPIO_NUM_43  // U2 Pad 8  (GPIO43) -> U13 Pin 9  (HELM1_EN)
#define PIN_MAIN_HELM2_EN               GPIO_NUM_44  // U2 Pad 29 (GPIO44) -> U14 Pin 9  (HELM2_EN)

// Backwards compatibility aliases
#define PIN_MAIN_A2DP_UART_TX           PIN_MAIN_HELM1_UART_TX
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
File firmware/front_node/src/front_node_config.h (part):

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#define SW3526_I2C_ADDR         0x3C         // SW3526 Fast Charge Controller I2C Address

// MK1 (Knowles SPH0645LM4H-B) & J_SENSOR_EXT (6-Pin: 1=3V3, 2=GND, 3=SDA, 4=SCL, 5=MIC_DATA, 6=MIC_WS)
#define PIN_MIC_I2S_WS          GPIO_NUM_4   // U1 GPIO4  -> MK1 Pin 2 & J_SENSOR_EXT Pin 6 (MIC_I2S_WS)
#define PIN_MIC_I2S_BCLK        GPIO_NUM_5   // U1 GPIO5  -> MK1 Pin 3 (MIC_I2S_BCLK)
#define PIN_MIC_I2S_DATA        GPIO_NUM_35  // U1 Pad 12 (GPIO35) -> MK1 Pin 1 & J_SENSOR_EXT Pin 5 (MIC_I2S_DATA)

// J_POD_L & J_POD_R Wired Handlebar / Mirror Pod Buttons (Active Low)
#define PIN_BTN_SIG_L_N         GPIO_NUM_8   // U1 GPIO8  -> J_POD_L Pin 3 (BTN_SIG_L_N: Intercom PTT / HFP)
#define PIN_BTN_SIG_R_N         GPIO_NUM_9   // U1 GPIO9  -> J_POD_R Pin 3 (BTN_SIG_R_N: Action-Cam / Mode)
#define PIN_PTT_IN1_N           PIN_BTN_SIG_L_N
#define PIN_PTT_IN2_N           PIN_BTN_SIG_R_N

// U2 Feasycom FSC-BT802 (CSR8670) Bluetooth 5.1 Infotainment Bridge & SkylineOS / Boom! Box Audio Mux
#define PIN_FRONT_BT_EN         GPIO_NUM_57  // U1 Pad 39 (GPIO57) -> U2 Pin 3 (BT_EN / Power Enable)
#define PIN_FRONT_BT_RST        GPIO_NUM_56  // U1 Pad 38 (GPIO56) -> U2 Pin 4 (BT_RST / Hardware Reset)
#define PIN_FRONT_BT_UART_RX    GPIO_NUM_43  // U1 GPIO43 -> U2 TX (AT Command UART RX)
#define PIN_FRONT_BT_UART_TX    GPIO_NUM_44  // U1 GPIO44 -> U2 RX (AT Command UART TX)
#define PIN_FRONT_BT_I2S_BCLK   GPIO_NUM_10  // U1 GPIO10 -> U2 I2S Bit Clock
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#define PIN_C3_I2S_SDI          PIN_FRONT_BT_I2S_DIN

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#define PIN_I2C_SDA             GPIO_NUM_22  // U1 Pad 17 (GPIO22) -> J_SENSOR_EXT Pin 3, J_DISP_L/R Pin 4 (I2C_SDA)
#define PIN_I2C_SCL             GPIO_NUM_23  // U1 Pad 18 (GPIO23) -> J_SENSOR_EXT Pin 4, J_DISP_L/R Pin 3 (I2C_SCL)
#define PIN_GNSS_RESET_N        GPIO_NUM_7   // U1 Pad 11 (GPIO7)  -> J_SENSOR_EXT Pin 8 (GNSS_RESET_N, Active-Low)
#define I2C_ADDR_OLED_LEFT      0x3C         // J_DISP_L Left Speaker-Corner Cockpit OLED
#define I2C_ADDR_OLED_RIGHT     0x3D         // J_DISP_R Right Speaker-Corner Cockpit OLED
#define I2C_ADDR_BMP390_BARO    0x76         // Sensor Puck BMP390 Barometer/Altimeter

// LED1 (WS2812B-2020), Q1 (DMN63D8 Dual MOSFET Mirror BSD LEDs) & Q2 (TPS1H100 Aux Light)
#define PIN_WS2812B_DIN         GPIO_NUM_24  // U1 Pad 19 (GPIO24) -> LED1 Pin 4 (WS2812B_DIN)
#define PIN_BSD_LED_LEFT        GPIO_NUM_25  // U1 Pad 20 (GPIO25) -> Q1 Pin 2 -> J_POD_L Pin 2 (BSD_LED_LEFT)
#define PIN_BSD_LED_RIGHT       GPIO_NUM_26  // U1 Pad 21 (GPIO26) -> Q1 Pin 5 -> J_POD_R Pin 2 (BSD_LED_RIGHT)
#define PIN_AUX_LIGHT_EN        GPIO_NUM_27  // U1 Pad 22 (GPIO27) -> Q2 Pin 3 -> J_AUX_LIGHT Pin 1 (AUX_LIGHT_EN)

// U1 Native High-Speed USB 2.0 PHY (480 Mbps) -> J1 Pins 3 & 4 (Direct 4-Wire Central Box Backbone)
#define PIN_USB_HS_DM           GPIO_NUM_19  // U1 Pad 54 -> J1 Pin 4 (USB_HS_DM)
#define PIN_USB_HS_DP           GPIO_NUM_20  // U1 Pad 55 -> J1 Pin 3 (USB_HS_DP)

// U9 (ESP32-E22-WROOM-2X2) 4-Bit SDIO 3.0 Wi-Fi 6E (5 GHz / 6 GHz) Co-Processor Interface
#define PIN_E22_SDIO_CLK        GPIO_NUM_35  // U1 Pad 30 -> U9 Pin 10 (SDIO_CLK)
#define PIN_E22_SDIO_CMD        GPIO_NUM_36  // U1 Pad 31 -> U9 Pin 11 (SDIO_CMD)
#define PIN_E22_SDIO_D0         GPIO_NUM_37  // U1 Pad 32 -> U9 Pin 12 (SDIO_D0)
#define PIN_E22_SDIO_D1         GPIO_NUM_38  // U1 Pad 33 -> U9 Pin 13 (SDIO_D1)
#define PIN_E22_SDIO_D2         GPIO_NUM_39  // U1 Pad 34 -> U9 Pin 14 (SDIO_D2)
#define PIN_E22_SDIO_D3         GPIO_NUM_40  // U1 Pad 35 -> U9 Pin 15 (SDIO_D3)
#define PIN_E22_IRQ             GPIO_NUM_60  // U1 Pad 37 (GPIO60) -> U9 Pin 16 (E22_IRQ)
#define PIN_E22_EN              GPIO_NUM_59  // U1 Pad 36 (GPIO59) -> U9 Pin 3 (E22_EN)

// --- 2. ESP32-E22 Wi-Fi 6E (5 GHz / 6 GHz) Cockpit Gateway Configuration ---
#define COCKPIT_WIFI_AP_SSID        "OpenMotorBridge-6E"
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
// Handlebar Button Identifier (J_POD_L / J_POD_R)
enum HandlebarButtonId : uint8_t {
    BTN_INTERCOM_PTT         = 0x01,   // J_POD_L Pin 3 (BTN_SIG_L_N)
    BTN_CAM_HIGHLIGHT        = 0x02,   // J_POD_R Pin 3 (BTN_SIG_R_N)
    BTN_MEDIA_VOICE          = 0x03
};

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
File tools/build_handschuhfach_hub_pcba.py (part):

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			(property "Footprint" "Package_DFN_QFN:QFN-36-1EP_6x6mm_P0.5mm_EP4.1x4.1mm" (at 0 0 0) (effects (font (size 1.27 1.27)) hide))
			(symbol "USB2514Bi_1_1"
				(rectangle (start -15.24 22.86) (end 15.24 -22.86) (stroke (width 0.254) (type solid)) (fill (type background)))
				(pin input line (at -17.78 20.32 0) (length 2.54) (name "USB_UP_DP" (effects (font (size 1.27 1.27)))) (number "21" (effects (font (size 1.27 1.27)))))
				(pin input line (at -17.78 17.78 0) (length 2.54) (name "USB_UP_DM" (effects (font (size 1.27 1.27)))) (number "20" (effects (font (size 1.27 1.27)))))
				(pin input line (at -17.78 12.70 0) (length 2.54) (name "VBUS_DET" (effects (font (size 1.27 1.27)))) (number "24" (effects (font (size 1.27 1.27)))))
				(pin input line (at -17.78 7.62 0) (length 2.54) (name "RESET_N" (effects (font (size 1.27 1.27)))) (number "33" (effects (font (size 1.27 1.27)))))
				(pin input line (at -17.78 2.54 0) (length 2.54) (name "XTAL_IN" (effects (font (size 1.27 1.27)))) (number "12" (effects (font (size 1.27 1.27)))))
				(pin output line (at -17.78 0.00 0) (length 2.54) (name "XTAL_OUT" (effects (font (size 1.27 1.27)))) (number "13" (effects (font (size 1.27 1.27)))))
				(pin passive line (at -17.78 -5.08 0) (length 2.54) (name "RBIAS" (effects (font (size 1.27 1.27)))) (number "36" (effects (font (size 1.27 1.27)))))
				(pin input line (at -17.78 -10.16 0) (length 2.54) (name "CFG_SEL0" (effects (font (size 1.27 1.27)))) (number "23" (effects (font (size 1.27 1.27)))))
				(pin input line (at -17.78 -12.70 0) (length 2.54) (name "CFG_SEL1" (effects (font (size 1.27 1.27)))) (number "25" (effects (font (size 1.27 1.27)))))
				(pin input line (at -17.78 -15.24 0) (length 2.54) (name "NON_REM0" (effects (font (size 1.27 1.27)))) (number "26" (effects (font (size 1.27 1.27)))))
				(pin input line (at -17.78 -17.78 0) (length 2.54) (name "NON_REM1" (effects (font (size 1.27 1.27)))) (number "27" (effects (font (size 1.27 1.27)))))
				(pin input line (at -17.78 -20.32 0) (length 2.54) (name "TEST" (effects (font (size 1.27 1.27)))) (number "28" (effects (font (size 1.27 1.27)))))
				(pin bidi line (at 17.78 20.32 180) (length 2.54) (name "USB_DN1_DP" (effects (font (size 1.27 1.27)))) (number "2" (effects (font (size 1.27 1.27)))))
				(pin bidi line (at 17.78 17.78 180) (length 2.54) (name "USB_DN1_DM" (effects (font (size 1.27 1.27)))) (number "1" (effects (font (size 1.27 1.27)))))
				(pin bidi line (at 17.78 12.70 180) (length 2.54) (name "USB_DN2_DP" (effects (font (size 1.27 1.27)))) (number "4" (effects (font (size 1.27 1.27)))))
				(pin bidi line (at 17.78 10.16 180) (length 2.54) (name "USB_DN2_DM" (effects (font (size 1.27 1.27)))) (number "3" (effects (font (size 1.27 1.27)))))
				(pin bidi line (at 17.78 5.08 180) (length 2.54) (name "USB_DN3_DP" (effects (font (size 1.27 1.27)))) (number "7" (effects (font (size 1.27 1.27)))))
				(pin bidi line (at 17.78 2.54 180) (length 2.54) (name "USB_DN3_DM" (effects (font (size 1.27 1.27)))) (number "6" (effects (font (size 1.27 1.27)))))
				(pin bidi line (at 17.78 -2.54 180) (length 2.54) (name "USB_DN4_DP" (effects (font (size 1.27 1.27)))) (number "9" (effects (font (size 1.27 1.27)))))
				(pin bidi line (at 17.78 -5.08 180) (length 2.54) (name "USB_DN4_DM" (effects (font (size 1.27 1.27)))) (number "8" (effects (font (size 1.27 1.27)))))
				(pin power_in line (at 0 25.4 270) (length 2.54) (name "VDD33" (effects (font (size 1.27 1.27)))) (number "5" (effects (font (size 1.27 1.27)))))
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
    place_fp("Connector_USB.pretty", "USB_C_Receptacle_HRO_TYPE-C-31-M-12", "J1", "SKYLINE_HOST",
             53.18, 15.70, 0,
             usbc_pins("VBUS_HOST_SENSE", "USB_UP_DP", "USB_UP_DM", "NET_J1_CC1", "NET_J1_CC2"),
             model_3d=usbc_3d)

    place_fp("Connector_USB.pretty", "USB_C_Receptacle_HRO_TYPE-C-31-M-12", "J2", "FRONT_NODE",
             39.68, 15.70, 0,
             usbc_pins("VCC_5V", "USB_DN3_DP", "USB_DN3_DM", "NET_J2_CC1", "NET_J2_CC2"),
             model_3d=usbc_3d)

    place_fp("Connector_USB.pretty", "USB_C_Receptacle_HRO_TYPE-C-31-M-12", "J3", "PHONE_CHARGE",
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
    place_fp("Connector_USB.pretty", "USB_C_Receptacle_HRO_TYPE-C-31-M-12", "J4", "DONGLE",
             45.82, 4.55, 180,
             usbc_pins("VCC_5V", "USB_DN1_DP", "USB_DN1_DM", "NET_J4_CC1", "NET_J4_CC2"),
             model_3d=usbc_3d)

    place_fp("Connector_USB.pretty", "USB_C_Receptacle_HRO_TYPE-C-31-M-12", "J5", "MEDIA",
             57.82, 4.55, 180,
             usbc_pins("VCC_5V", "USB_DN2_DP", "USB_DN2_DM", "NET_J5_CC1", "NET_J5_CC2"),
             model_3d=usbc_3d)

    # U1: Microchip USB2514B Automotive 4-Port Hub Controller at (69.25, 6.4125), rot = 0°
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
